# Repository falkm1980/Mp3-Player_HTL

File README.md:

# Mp3-Player_HTL
MP3 Player, HTL Saalfelden

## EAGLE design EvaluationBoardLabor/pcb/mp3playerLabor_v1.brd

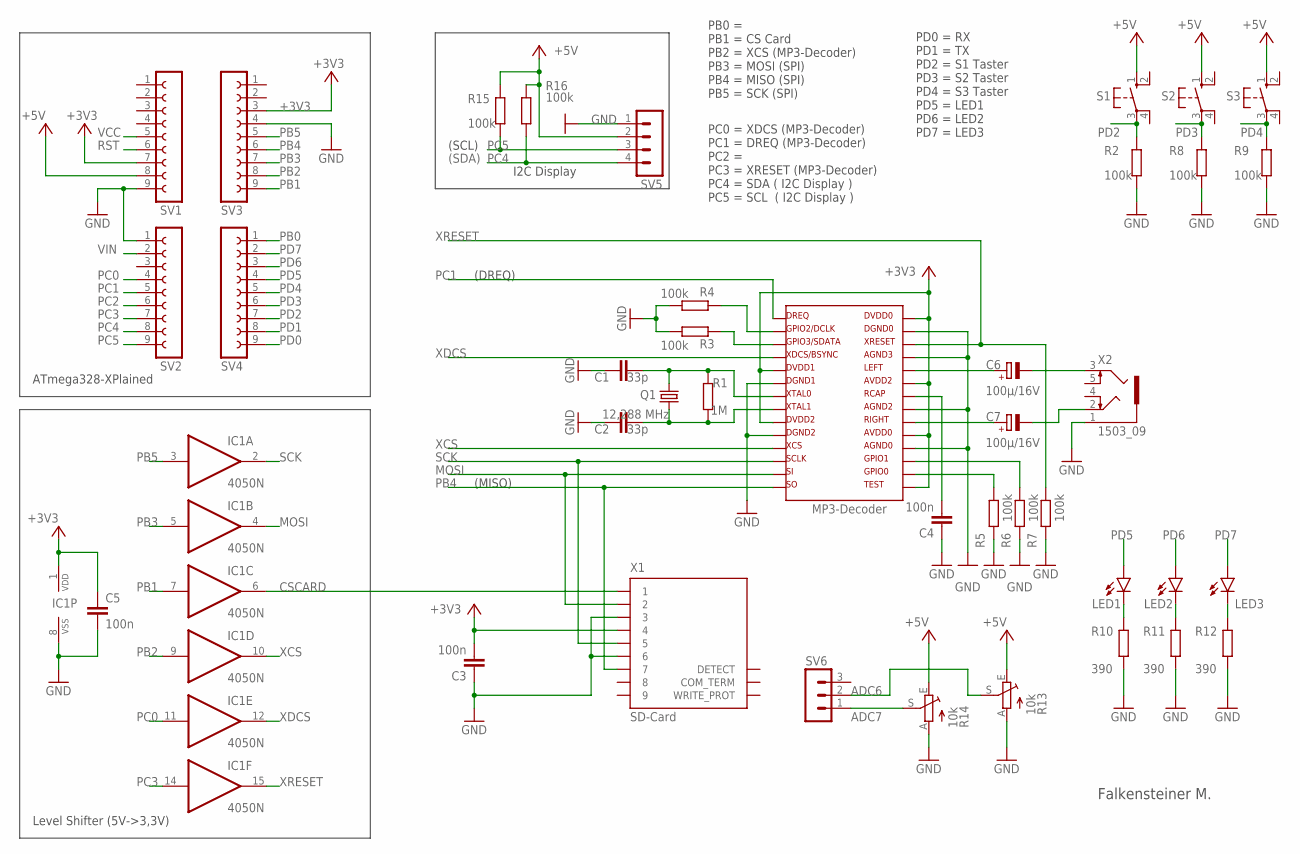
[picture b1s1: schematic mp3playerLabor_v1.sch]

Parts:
C1, C2: 33p; C1206K
C3, C4, C5: 100n; C1206K
C6, C7: 100µ/16V; UD-6,3X7,7_NICHICON
IC1: 4050N; DIL16
LED1, LED2, LED3: LEDSML1206; SML1206
Q1: 12,288 MHz; HC49UP
R1: 1M; R1206
R2, R3, R4, R5, R6, R7, R8, R9, R15, R16: 100k; R1206
R10, R11, R12: 390; R1206
R13, R14: 10k; CA6V
S1, S2, S3: 10-XX; B3F-10XX
SV1, SV2, SV3, SV4: FE09-1; FE09
SV5: MA04-1
SV6: MA03-1
U$1: VS1011; SOIC-28
X1: SD-Card; FPS009-3000
X2: 1503_09

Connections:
+3V3: C3.2, C5.1, IC1.1 (VDD), SV1.7, SV3.3, U$1.5, U$1.9, U$1.15, U$1.19, U$1.23, U$1.28, X1.4
+5V: R13.E, R14.E, R15.1, R16.1, S1.1 (S), S2.1 (S), S3.1 (S), SV1.8, SV5.2
ADC6: R13.S, SV6.2
ADC7: R14.S, SV6.1
CSCARD: IC1.6 (O), X1.1
GND: C1.1, C2.1, C3.1, C4.1, C5.2, IC1.8 (VSS), R2.2, R3.2, R4.2, R5.2, R6.2, R7.2, R8.2, R9.2, R10.2, R11.2, R12.2, R13.A, R14.A, SV1.9, SV2.1, SV3.4, SV5.1, U$1.6, U$1.10, U$1.18, U$1.21, U$1.25, U$1.27, X1.3, X1.6, X2.1
MOSI: IC1.4 (O), U$1.13, X1.2
unnamed: LED1.C, R10.1
unnamed: LED2.C, R11.1
unnamed: C2.2, Q1.1, R1.1, U$1.8
unnamed: LED3.C, R12.1
unnamed: C4.2, U$1.22
unnamed: R3.1, U$1.3
unnamed: C1.2, Q1.2, R1.2, U$1.7
unnamed: R4.1, U$1.2
unnamed: R6.1, U$1.17
unnamed: R5.1, U$1.16
unnamed: C7.+, U$1.20
unnamed: C6.+, U$1.24
unnamed: C6.-, X2.3
unnamed: C7.-, X2.2
PB0: SV4.1
PB1: IC1.7 (I), SV3.9
PB2: IC1.9 (I), SV3.8
PB3: IC1.5 (I), SV3.7
PB4: SV3.6, U$1.14, X1.7
PB5: IC1.3 (I), SV3.5
PC0: IC1.11 (I), SV2.4
PC1: SV2.5, U$1.1
PC2: SV2.6
PC3: IC1.14 (I), SV2.7
PC4: R16.2, SV2.8, SV5.4
PC5: R15.2, SV2.9, SV5.3
PD0: SV4.9
PD1: SV4.8
PD2: R2.1, S1.3, SV4.7
PD3: R8.1, S2.3, SV4.6
PD4: R9.1, S3.3, SV4.5
PD5: LED1.A, SV4.4
PD6: LED2.A, SV4.3
PD7: LED3.A, SV4.2
RST: SV1.6
SCK: IC1.2 (O), U$1.12, X1.5
VCC: SV1.5
VIN: SV2.2
XCS: IC1.10 (O), U$1.11
XDCS: IC1.12 (O), U$1.4
XRESET: IC1.15 (O), R7.1, U$1.26

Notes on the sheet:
Falkensteiner M.
PB0 = PB1 = CS Card PB2 = XCS (MP3-Decoder) PB3 = MOSI (SPI) PB4 = MISO (SPI) PB5 = SCK (SPI)
(MISO)
ATmega328-XPlained
PC0 = XDCS (MP3-Decoder) PC1 = DREQ (MP3-Decoder) PC2 = PC3 = XRESET (MP3-Decoder) PC4 = SDA ( I2C Display ) PC5 = SCL ( I2C Display )
Level Shifter (5V->3,3V)
PD0 = RX PD1 = TX PD2 = S1 Taster PD3 = S2 Taster PD4 = S3 Taster PD5 = LED1 PD6 = LED2 PD7 = LED3
MP3-Decoder
(DREQ)
(SCL)
(SDA)
I2C Display

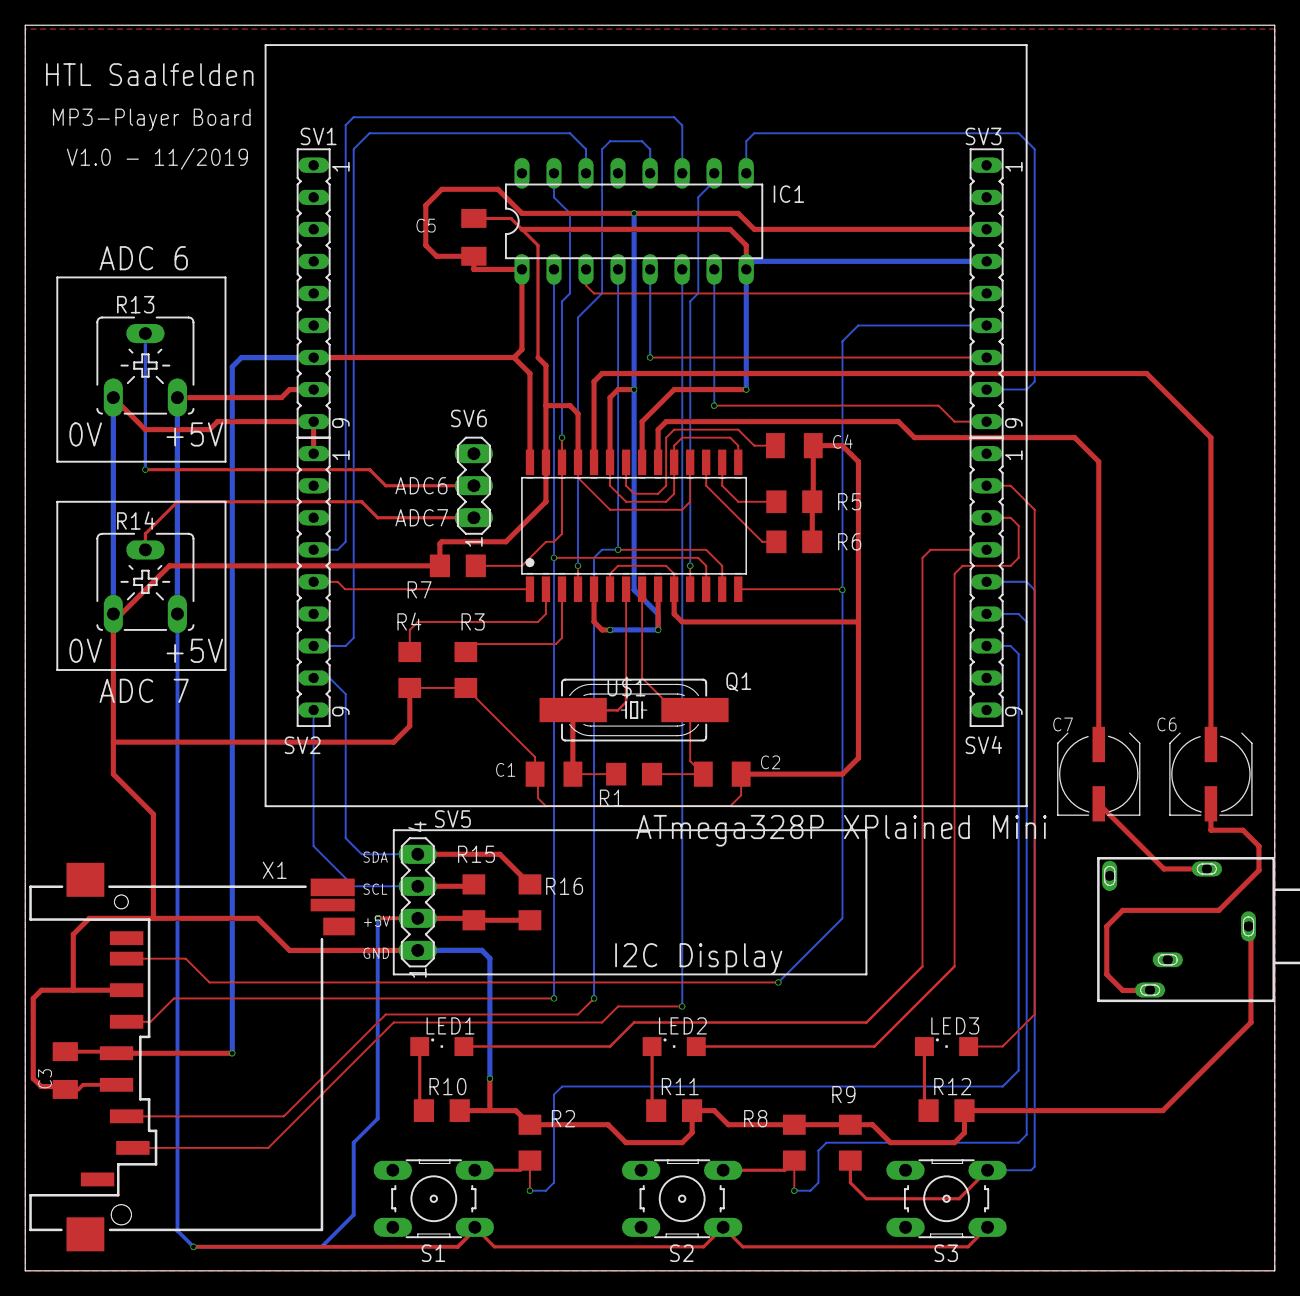
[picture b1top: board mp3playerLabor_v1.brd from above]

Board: 2 copper layers, 99.0 x 98.7 mm, 40 parts (0 on the bottom side), 41 nets.

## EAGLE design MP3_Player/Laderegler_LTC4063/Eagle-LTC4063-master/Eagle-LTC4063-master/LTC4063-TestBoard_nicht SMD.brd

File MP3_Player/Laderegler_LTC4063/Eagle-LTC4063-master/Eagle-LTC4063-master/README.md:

Eagle library for LTC4063
=========================

> Standalone Linear Li-Ion Charger with Micropower Low Dropout Linear Regulator

Eagle (v6.3) library for the LTC4063 Li-Ion Charger by Linear Technology. 

- Datasheet: http://cds.linear.com/docs/en/datasheet/4063fc.pdf
- Product Page: http://www.linear.com/product/LTC4063

License
-------

You are allowed to use the library for everything you want (including the distribution of this files) as long as you keep the Copyright notice in the library.

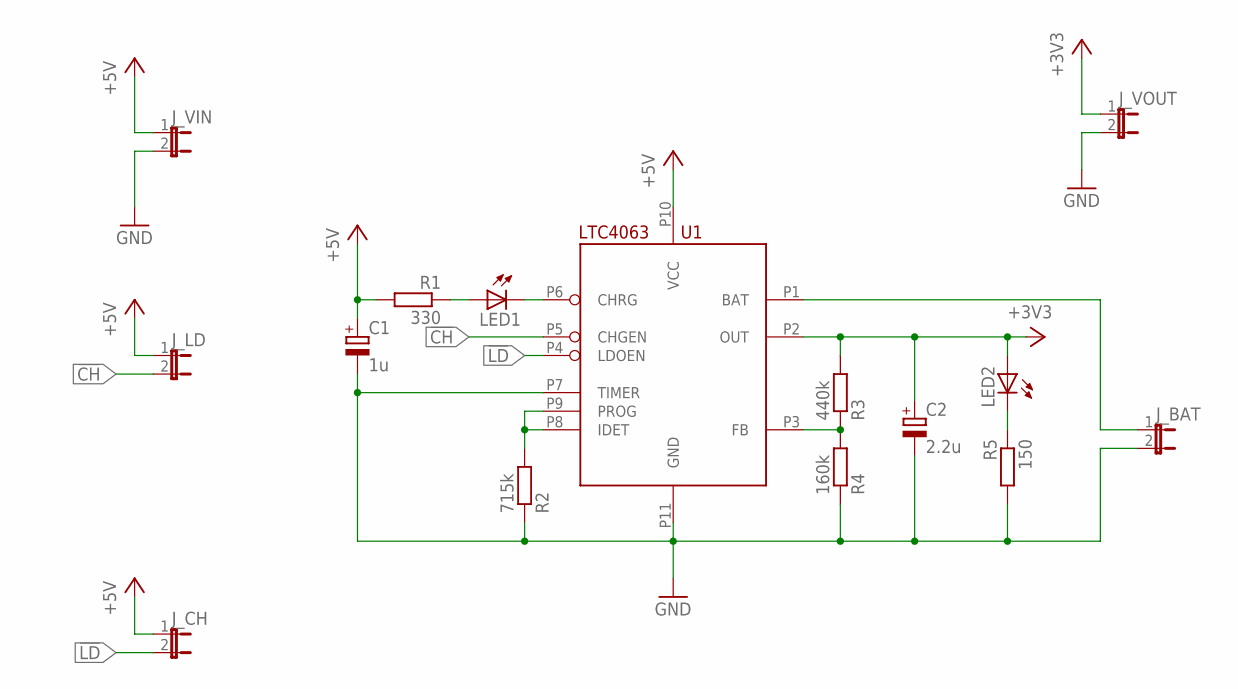
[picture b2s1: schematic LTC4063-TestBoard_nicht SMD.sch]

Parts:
C1: 1u; E2,5-6
C2: 2.2u; E2,5-6
J_BAT: JP1E; JP1
J_CH: JP1E; JP1
J_LD: JP1E; JP1
J_VIN: JP1E; JP1
J_VOUT: JP1E; JP1
LED1, LED2: LED3MM
R1: 330; 0207/7
R2: 715k; 0207/7
R3: 440k; 0207/7
R4: 160k; 0207/7
R5: 150; 0207/7
U1: LTC4063

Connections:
!CH: J_LD.2, U1.P5 (CHGEN)
!LD: J_CH.2, U1.P4 (LDOEN)
+3V3: C2.+, J_VOUT.1, LED2.A, R3.2, U1.P2 (OUT)
+5V: C1.+, J_CH.1, J_LD.1, J_VIN.1, R1.2, U1.P10 (VCC)
GND: C1.-, C2.-, J_BAT.2, J_VIN.2, J_VOUT.2, R2.1, R4.1, R5.2, U1.P7 (TIMER), U1.P11 (GND)
unnamed: R3.1, R4.2, U1.P3 (FB)
unnamed: J_BAT.1, U1.P1 (BAT)
unnamed: LED1.K (C), U1.P6 (CHRG)
unnamed: LED1.A, R1.1
unnamed: R2.2, U1.P8 (IDET), U1.P9 (PROG)
unnamed: LED2.K (C), R5.1

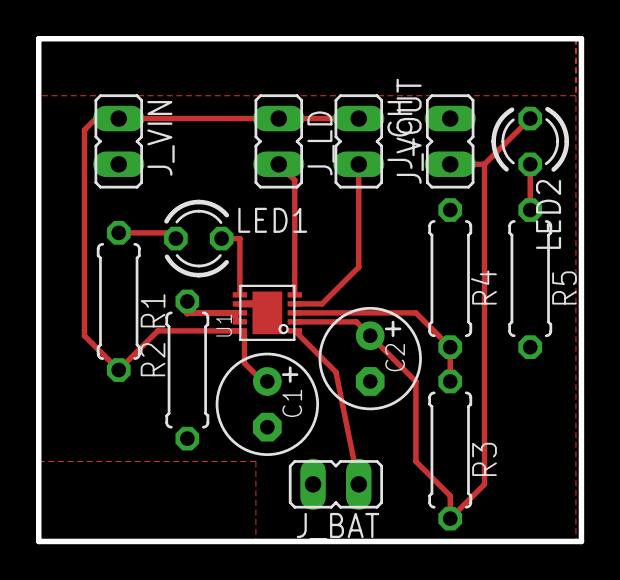
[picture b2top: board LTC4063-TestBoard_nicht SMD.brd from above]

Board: 2 copper layers, 30.1 x 27.9 mm, 15 parts (0 on the bottom side), 11 nets.

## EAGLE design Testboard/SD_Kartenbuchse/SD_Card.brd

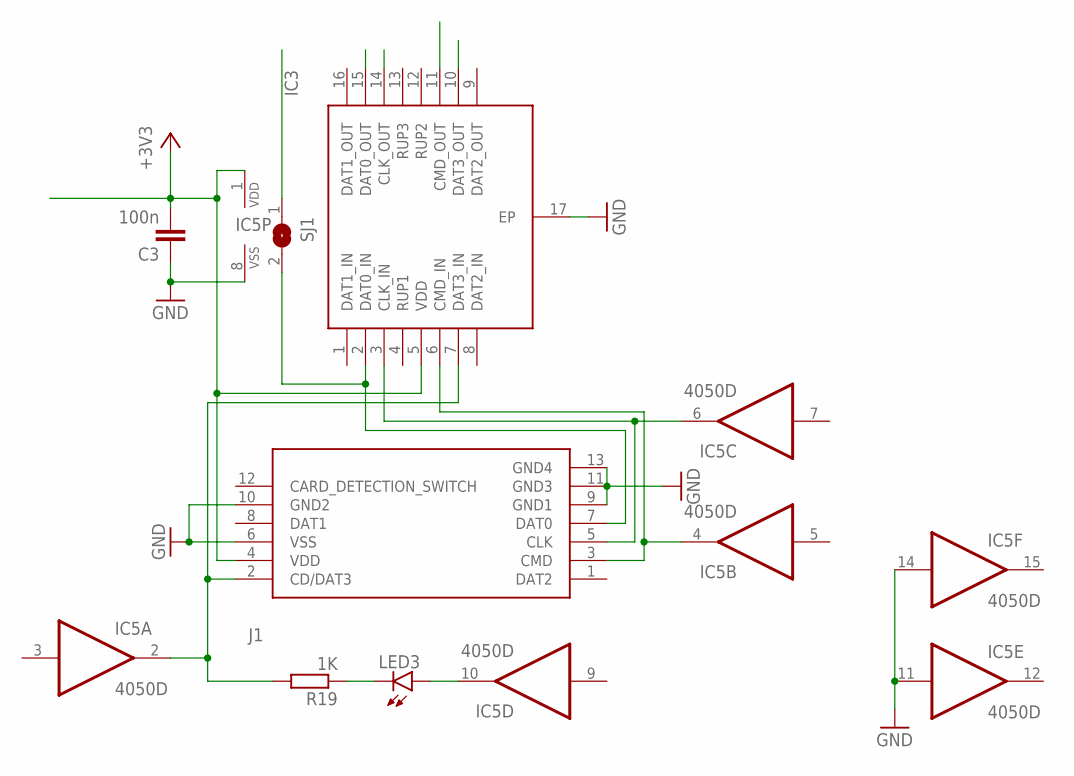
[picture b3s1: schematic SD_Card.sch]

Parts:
C3: 100n; C1206K
IC3: ECLAMP2410P.TCT; SON50P160X400X65-17N
IC5: 4050D; SO16
J1: DM3CS-SF
LED3: LG_T679-E1F1-1; PLCC2
R19: 1K; R1206
SJ1: SJ

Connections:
+3V3: C3.2, IC3.5 (VDD), IC5.1 (VDD), J1.4 (VDD)
GND: C3.1, IC3.17 (EP), IC5.8 (VSS), IC5.11 (I), IC5.14 (I), J1.6 (VSS), J1.9 (GND1), J1.10 (GND2), J1.11 (GND3), J1.13 (GND4)
unnamed: IC3.15 (DAT0_OUT), SJ1.1
unnamed: IC5.10 (O), LED3.A
unnamed: LED3.C, R19.1
unnamed: IC3.7 (DAT3_IN), IC5.2 (O), J1.2 (CD/DAT3), R19.2
unnamed: IC3.2 (DAT0_IN), J1.7 (DAT0), SJ1.2
unnamed: IC3.3 (CLK_IN), IC5.6 (O), J1.5 (CLK)
unnamed: IC3.6 (CMD_IN), IC5.4 (O), J1.3 (CMD)

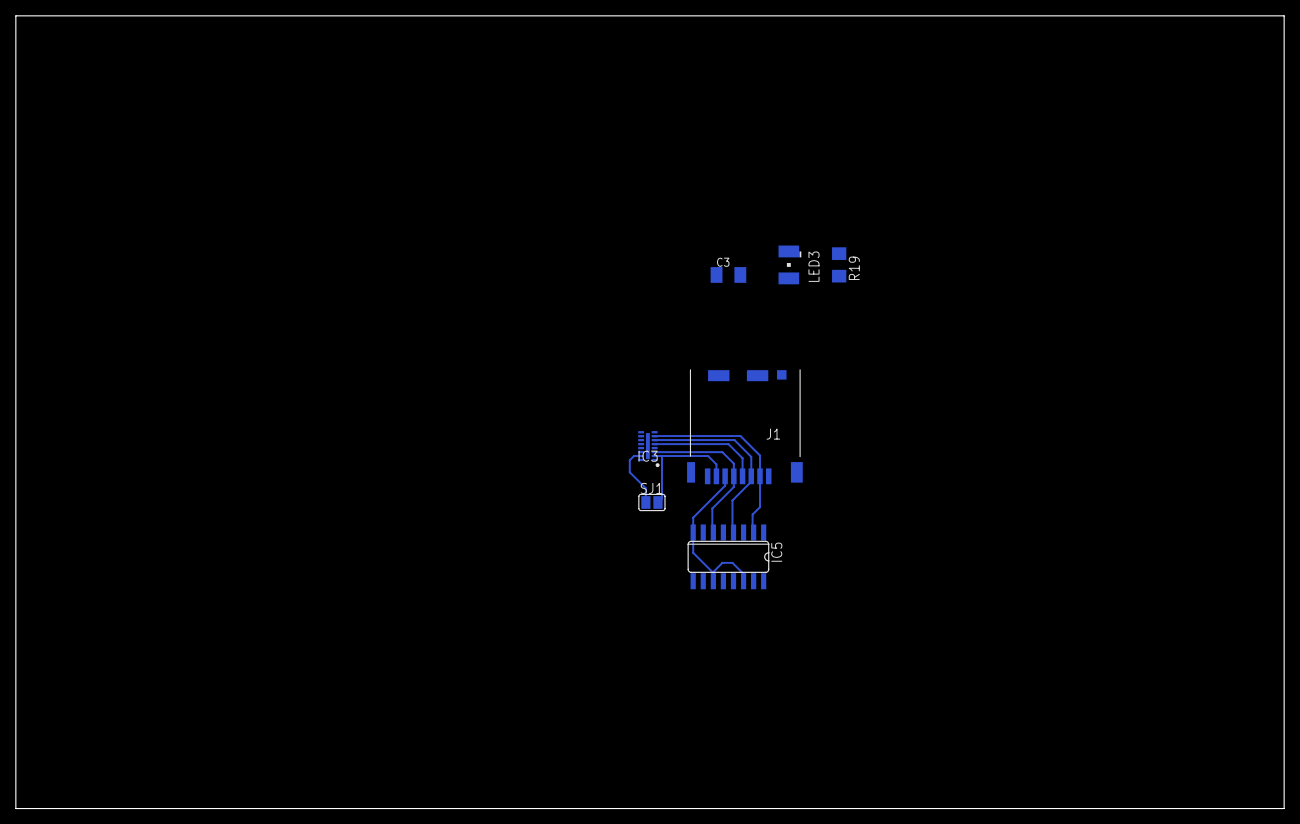
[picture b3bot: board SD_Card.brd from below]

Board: 2 copper layers, 160.0 x 100.0 mm, 7 parts (7 on the bottom side), 9 nets.

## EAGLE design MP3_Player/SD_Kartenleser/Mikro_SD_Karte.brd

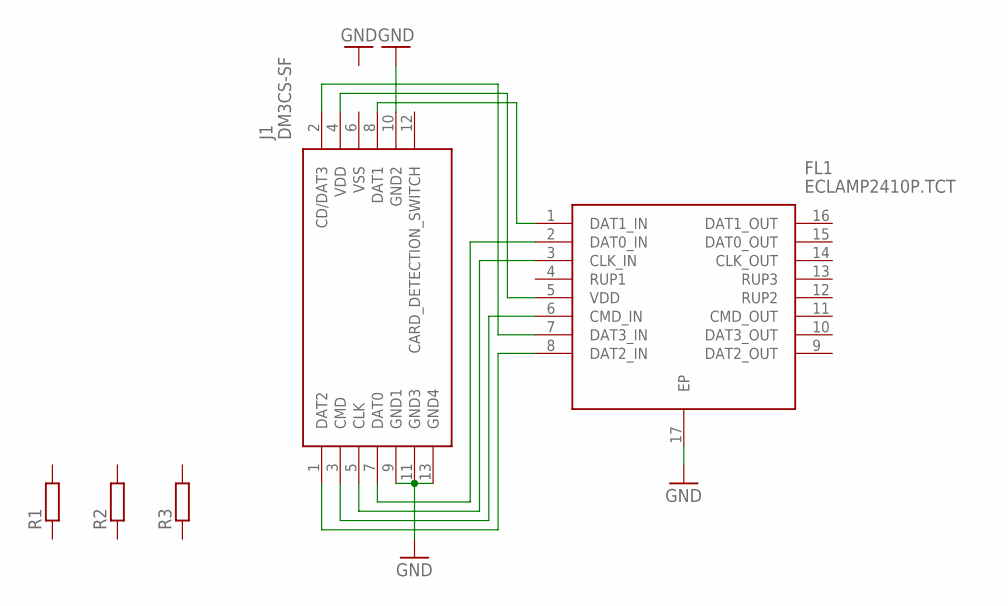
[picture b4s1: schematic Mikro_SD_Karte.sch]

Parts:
FL1: ECLAMP2410P.TCT; SON50P160X400X65-17N
J1: DM3CS-SF
R1, R2, R3: R-EU_R0603; R0603

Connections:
GND: FL1.17 (EP), J1.9 (GND1), J1.10 (GND2), J1.11 (GND3), J1.13 (GND4)
unnamed: FL1.1 (DAT1_IN), J1.8 (DAT1)
unnamed: FL1.8 (DAT2_IN), J1.1 (DAT2)
unnamed: FL1.5 (VDD), J1.4 (VDD)
unnamed: FL1.7 (DAT3_IN), J1.2 (CD/DAT3)
unnamed: FL1.2 (DAT0_IN), J1.7 (DAT0)
unnamed: FL1.3 (CLK_IN), J1.5 (CLK)
unnamed: FL1.6 (CMD_IN), J1.3 (CMD)

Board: 2 copper layers, 5 parts (0 on the bottom side), 8 nets, no tracks yet.

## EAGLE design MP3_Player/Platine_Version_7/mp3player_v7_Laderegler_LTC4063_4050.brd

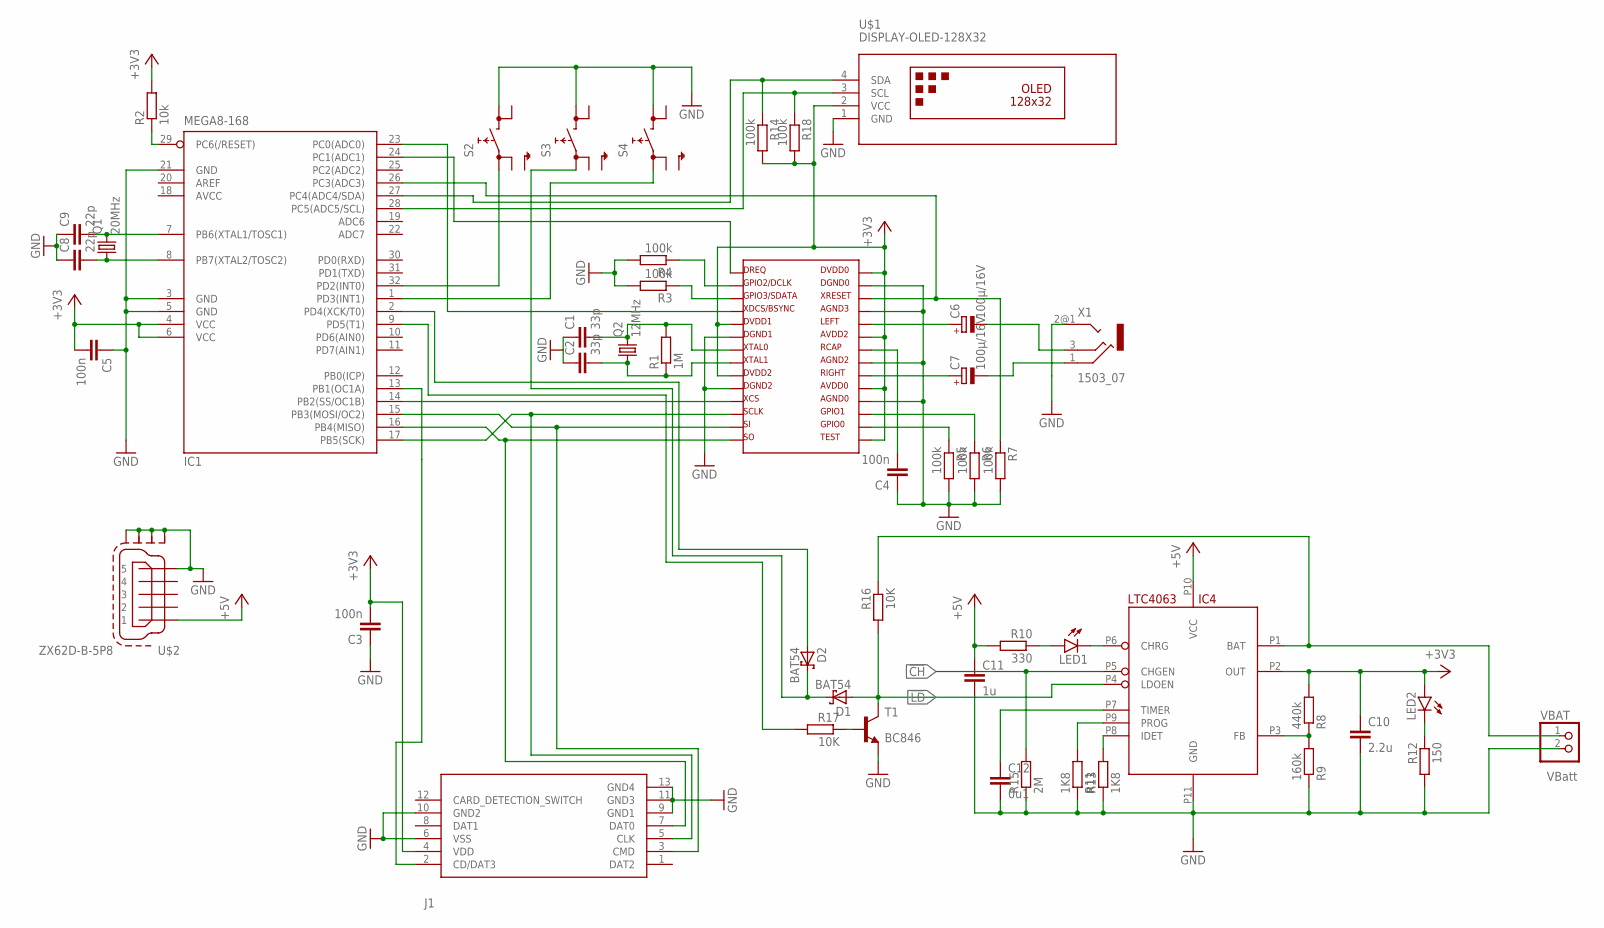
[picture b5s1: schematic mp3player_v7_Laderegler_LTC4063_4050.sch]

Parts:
C1, C2: 33p; C1206K
C3, C4, C5: 100n; C1206K
C6, C7: 100µ/16V; UD-6,3X7,7_NICHICON
C8, C9: 22p; C1206K
C10: 2.2u; C0805K
C11: 1u; C0805K
C12: 0u1; C0805K
D1, D2: BAT54; SOT23
IC1: MEGA8-168; TQFP32-08
IC2: VS1011; SOIC-28
IC4: LTC4063
J1: DM3CS-SF
LED1, LED2: LG_T679-E1F1-1; PLCC2
Q1: 20MHz; HC49UP
Q2: 12MHz; HC49UP
R1: 1M; R0805
R2: 10k; 0207/7
R3, R4, R5, R6, R14, R18: 100k; R0805
R7: 100k; 0207/15
R8: 440k; R0805
R9: 160k; R0805
R10: 330; R0805
R11, R13: 1K8; R0805
R12: 150; R0805
R15: 2M; R0805
R16: 10K; 0207/7
R17: 10K; R0805
S2, S3, S4: SKHMPSE010; SKHMPXE010
T1: BC846; SOT23
U$1: DISPLAY-OLED-128X32
U$2: ZX62D-B-5P8
VBAT: PINHD-1X2; 1X02
X1: 1503_07

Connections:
!CH: IC4.P5 (CHGEN), R15.2
!LD: D1.1 (A), IC4.P4 (LDOEN), R16.2, T1.3 (C)
+3V3: C3.2, C5.2, C10.1, IC1.4 (VCC), IC1.6 (VCC), IC2.5, IC2.9, IC2.15, IC2.19, IC2.23, IC2.28, IC4.P2 (OUT), J1.4 (VDD), LED2.A, R2.2, R8.2, R14.2, R18.2, U$1.2 (VCC)
+5V: C11.1, IC4.P10 (VCC), R10.2, U$2.P$1 (1)
AVCC: IC1.18 (AVCC)
GND: C1.1, C2.1, C3.1, C4.1, C5.1, C8.1, C9.1, C10.2, C11.2, C12.2, IC1.3 (GND), IC1.5 (GND), IC1.21 (GND), IC2.6, IC2.10, IC2.18, IC2.21, IC2.25, IC2.27, IC4.P11 (GND), J1.6 (VSS), J1.9 (GND1), J1.10 (GND2), J1.11 (GND3), J1.13 (GND4), R3.2, R4.2, R5.2, R6.2, R7.2, R9.1, R11.1, R12.2, R13.1, R15.1, S2.3 (2.1), S3.3 (2.1), S4.3 (2.1), T1.2 (E), U$1.1 (GND), U$2.P$5 (5), U$2.SH1, U$2.SH2, U$2.SH3, U$2.SH4, VBAT.2, X1.2@1 (2)
unnamed: IC1.17 (PB5(SCK)), IC2.12, J1.5 (CLK)
unnamed: IC1.16 (PB4(MISO)), IC2.14, J1.7 (DAT0)
unnamed: IC1.15 (PB3(MOSI/OC2)), IC2.13, J1.3 (CMD)
unnamed: IC1.14 (PB2(SS/OC1B)), IC2.11
unnamed: C2.2, IC2.8, Q2.1, R1.1
unnamed: IC1.23 (PC0(ADC0)), IC2.4
unnamed: C4.2, IC2.22
unnamed: IC2.3, R3.1
unnamed: C1.2, IC2.7, Q2.2, R1.2
unnamed: IC2.2, R4.1
unnamed: IC1.32 (PD2(INT0)), S2.1 (1.1)
unnamed: IC2.17, R6.1
unnamed: IC2.16, R5.1
unnamed: IC1.24 (PC1(ADC1)), IC2.1
unnamed: D2.1 (A), IC1.2 (PD4(XCK/T0))
unnamed: IC1.26 (PC3(ADC3)), IC2.26, R7.1
unnamed: IC1.29 (PC6(/RESET)), R2.1
unnamed: C7.+, IC2.20
unnamed: C6.+, IC2.24
unnamed: IC1.1 (PD3(INT1)), S4.1 (1.1)
unnamed: C6.-, X1.3
unnamed: C7.-, X1.1
unnamed: C8.2, IC1.8 (PB7(XTAL2/TOSC2)), Q1.1
unnamed: C9.2, IC1.7 (PB6(XTAL1/TOSC1)), Q1.2
unnamed: IC4.P3 (FB), R8.1, R9.2
unnamed: IC4.P1 (BAT), R16.1, VBAT.1
unnamed: LED1.A, R10.1
unnamed: IC4.P9 (PROG), R11.2
unnamed: IC4.P6 (CHRG), LED1.C
unnamed: LED2.C, R12.1
unnamed: IC4.P8 (IDET), R13.2
unnamed: C12.1, IC4.P7 (TIMER)
unnamed: IC1.27 (PC4(ADC4/SDA)), R14.1, U$1.4 (SDA)
unnamed: IC1.28 (PC5(ADC5/SCL)), R18.1, U$1.3 (SCL)
unnamed: IC1.13 (PB1(OC1A)), J1.2 (CD/DAT3)
unnamed: R17.1, T1.1 (B)
unnamed: IC1.9 (PD5(T1)), R17.2
unnamed: D1.3 (C), D2.3 (C), S3.1 (1.1)

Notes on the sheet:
VBatt

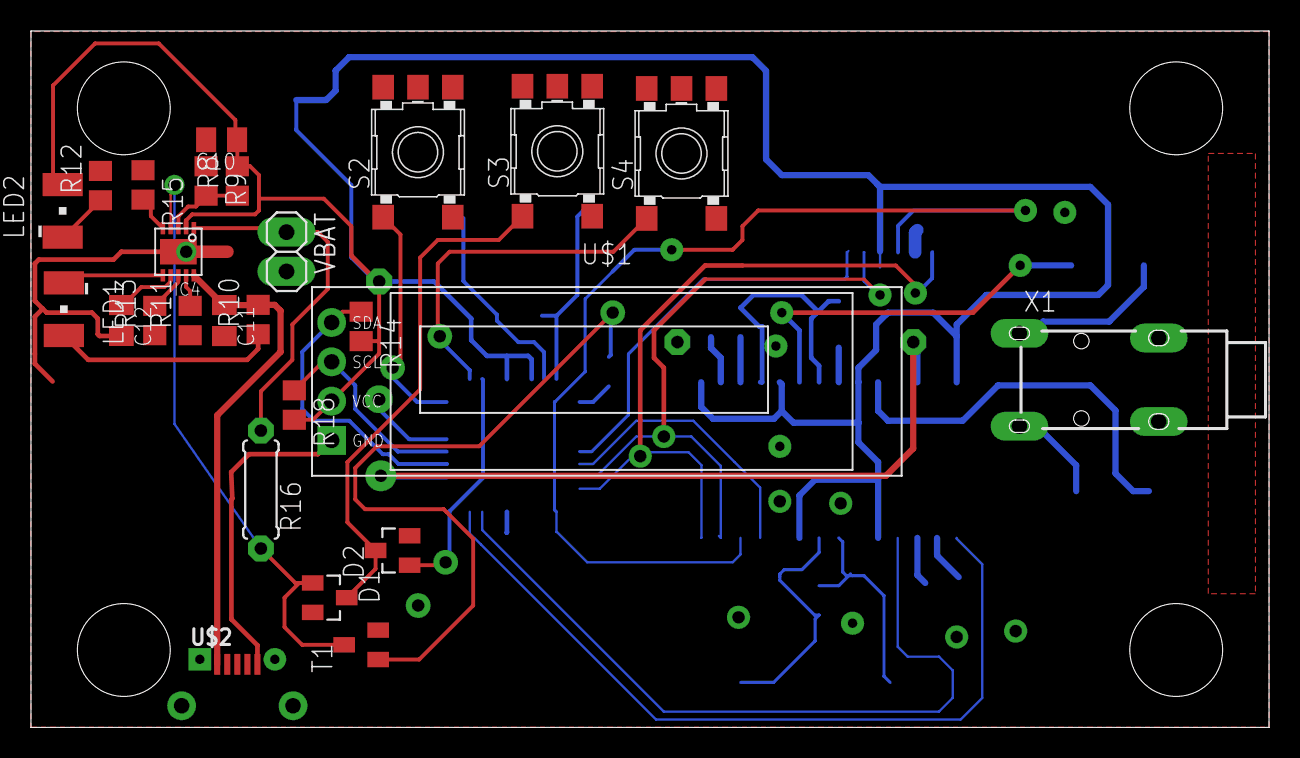
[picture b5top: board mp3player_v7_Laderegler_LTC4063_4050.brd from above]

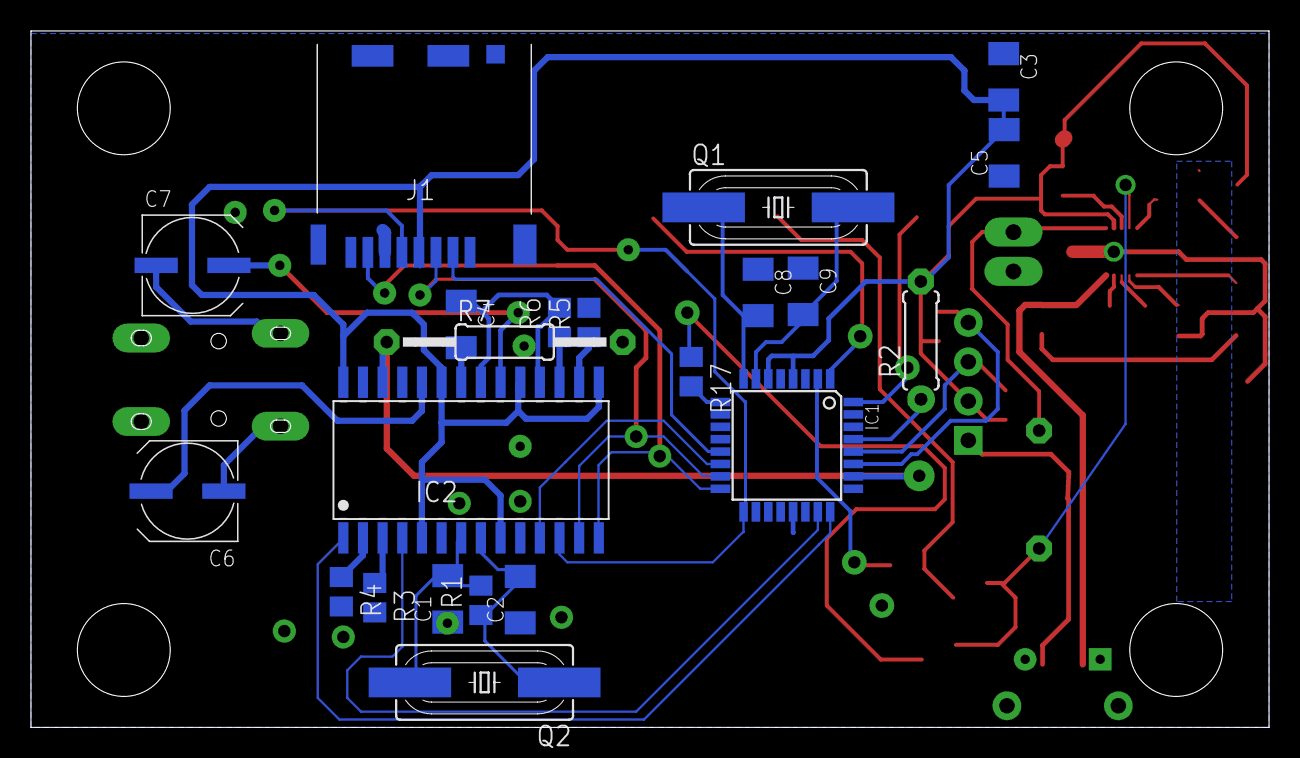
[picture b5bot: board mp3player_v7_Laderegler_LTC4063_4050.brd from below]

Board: 2 copper layers, 80.0 x 45.0 mm, 48 parts (22 on the bottom side), 43 nets.

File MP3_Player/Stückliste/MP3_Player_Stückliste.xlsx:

|  | Stückliste MP3 Player |  | RS |  |  |  | Bibliothek
Pos | Stück | Bezeichnung | Beschreibung | Bestellnummer | Gehäuse | Lieferant | Preis
 |  | ATMEGA 168 | Prozessor | 922-0749
 |  | VS1011E | Audio IC
 |  | BTM-222_Serial | Bluetooth
 |  | Quarz | 20MHz | 148-5634
 |  | Quarz | 12MHz | 148-5359
 |  | Klinkenbuchse |  | 909-2238 | Testboard | RS | 1.3859999999999999
 |  | Klinkenbuchse | RS | 513-0421 | Testboard | RS | 1.42 | con_Hirschmann
 |  | Klinkenbuchse | Reichelt | LUM1503-02 | SMD | Reichelt
 |  | Klinkenbuchse | Reichelt | LUM1503-07 | Draht | Reichelt
 |  | LTC3455 |  | 153-3383
 |  | Elko | 10µ | 136-2654 | 1206 |  | 0.158
 |  | Elko | 47µ | 136-2598 | 1206
 |  | Kondensator | 27pF | 169-9964
 |  | LED Rot |  | 862-4695 |  |  | 9.7000000000000003E-2
 |  | LED Grün |  | 862-4691 |  |  | 0.1
 |  | LTC4063 | Mouser
 |  | Accu | Conrad | 252031-62
 |  | Accu | Mouser | 406-ASR00035
 |  | Gehäuse | Nedis | BOX G404
 |  | Akku | Reichelt | Akku 30083
 |  | Akku | Reichelt | AKKU CP 38 | 500mA
 |  | USB | RS | 136-2263
 |  | C1 | 33p | Bestellnummer | R1206
 |  | C2 | 33p |  | R1206
 |  | C3 | 100n |  | R1206
 |  | C4 | 100n |  | R1206
 |  | C5 | 100n |  | R1206
 |  | C6 | 100µ/16V |  | DU-6,3x7,7
 |  | C7 | 100µ/16V |  | DU-6,3x7,8
 |  | C8 | 22p |  | R1206
 |  | C9 | 22p |  | R1206
 |  | C10 | 2,2µ |  | R0805
 |  | C11 | 1µ |  | R0805
 |  | C12 | 0,1µ |  | R0805
 |  | R1 | 1M |  | R0805
 |  | R2 | 10K |  | 0207/10
 |  | R3 | 100K |  | R1206
 |  | R4 | 100K |  | R1206
 |  | R5 | 100K |  | R0805
 |  | R6 | 100K |  | R0806
 |  | R7 | 100K |  | R1206
 |  | R8 | 440K |  | R0806
 |  | R9 | 160K |  | R0806
 |  | R10 | 330R |  | R0806
 |  | R11 | 1k8 |  | R0806
 |  | R12 | 150R |  | R0806
 |  | R13 | 1K8 |  | R1206
 |  | R14 | 100K |  | R0806
 |  | R15 | 2M |  | R0806
 |  | R16 | 10K |  | 0207/10
 |  | R17 | 10K |  | 0207/10
 |  | R18 | 100K |  | 0207/10
 |  | R19 | 1K |  | 0207/10

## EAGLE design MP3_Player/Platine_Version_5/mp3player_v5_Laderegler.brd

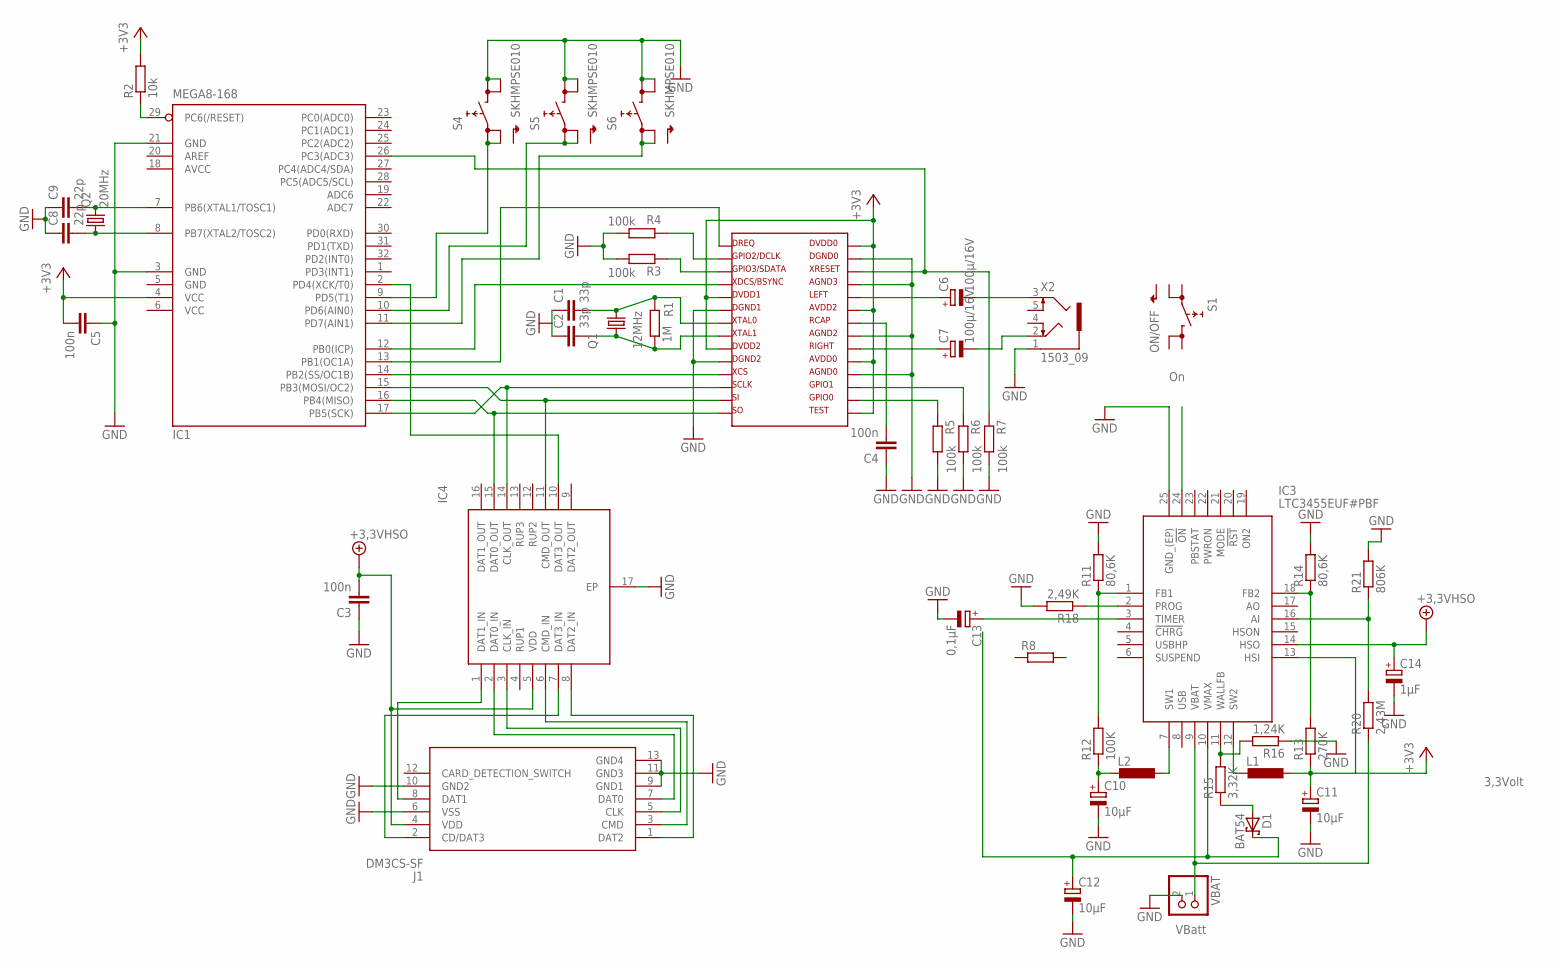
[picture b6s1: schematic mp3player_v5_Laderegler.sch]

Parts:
C1, C2: 33p; C1206K
C3, C4, C5: 100n; C1206K
C6, C7: 100µ/16V; UD-6,3X7,7_NICHICON
C8, C9: 22p; C1206K
C10, C11, C12: 10µF; 153CLV-0505
C13: 0,1µF; B/3528-21W
C14: 1µF; B/3528-21W
D1: BAT54; SOT23
IC1: MEGA8-168; TQFP32-08
IC2: VS1011; SOIC-28
IC3: LTC3455EUF#PBF; QFN50P400X400X80-25N
IC4: ECLAMP2410P.TCT; SON50P160X400X65-17N
J1: DM3CS-SF
L1, L2: L-EUL2825P; L2825P
Q1: 12MHz; HC49UP
Q2: 20MHz; HC49UP
R1: 1M; R0805
R2: 10k; R0805
R3, R4, R5, R6, R7: 100k; R0805
R8: R-EU_R0805; R0805
R11, R14: 80,6K; R0805
R12: 100K; M1206
R13: 270K; M1206
R15: 3,32K; M1206
R16: 1,24K; M1206
R18: 2,49K; R0805
R20: 2,43M; M1206
R21: 806K; R0805
S1: ON/OFF; SKHMPXE010
S4, S5, S6: SKHMPSE010; SKHMPXE010
VBAT: PINHD-1X2; 1X02
X2: 1503_09

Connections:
+3,3VHSO: C3.2, C14.+, IC3.14 (HSO), IC4.5 (VDD), J1.4 (VDD)
+3V3: C5.2, C11.+, IC1.4 (VCC), IC2.5, IC2.9, IC2.15, IC2.19, IC2.23, IC2.28, IC3.13 (HSI), L1.1, R2.2, R13.1
AVCC: IC1.18 (AVCC)
GND: C1.1, C2.1, C3.1, C4.1, C5.1, C8.1, C9.1, C10.-, C11.-, C12.-, C13.-, C14.-, IC1.3 (GND), IC1.5 (GND), IC1.21 (GND), IC2.6, IC2.10, IC2.18, IC2.21, IC2.25, IC2.27, IC3.25 (GND_(EP)), IC4.17 (EP), J1.6 (VSS), J1.9 (GND1), J1.10 (GND2), J1.11 (GND3), J1.13 (GND4), R3.2, R4.2, R5.2, R6.2, R7.2, R11.2, R14.2, R16.1, R18.2, R21.2, S4.3 (2.1), S4.4 (2.2), S5.3 (2.1), S5.4 (2.2), S6.3 (2.1), S6.4 (2.2), VBAT.2, X2.1
unnamed: IC1.17 (PB5(SCK)), IC2.12, IC4.14 (CLK_OUT)
unnamed: IC1.16 (PB4(MISO)), IC2.14, IC4.15 (DAT0_OUT)
unnamed: IC1.15 (PB3(MOSI/OC2)), IC2.13, IC4.11 (CMD_OUT)
unnamed: IC1.14 (PB2(SS/OC1B)), IC2.11
unnamed: IC1.2 (PD4(XCK/T0)), IC4.10 (DAT3_OUT)
unnamed: C2.2, IC2.8, Q1.1, R1.1
unnamed: IC1.12 (PB0(ICP)), IC2.4
unnamed: C4.2, IC2.22
unnamed: IC2.3, R3.1
unnamed: C1.2, IC2.7, Q1.2, R1.2
unnamed: IC2.2, R4.1
unnamed: IC1.9 (PD5(T1)), S4.1 (1.1), S4.2 (1.2)
unnamed: IC2.17, R6.1
unnamed: IC2.16, R5.1
unnamed: IC1.13 (PB1(OC1A)), IC2.1
unnamed: IC1.10 (PD6(AIN0)), S5.1 (1.1), S5.2 (1.2)
unnamed: IC1.26 (PC3(ADC3)), IC2.26, R7.1
unnamed: IC1.29 (PC6(/RESET)), R2.1
unnamed: C7.+, IC2.20
unnamed: C6.+, IC2.24
unnamed: IC1.11 (PD7(AIN1)), S6.1 (1.1), S6.2 (1.2)
unnamed: C6.-, X2.3
unnamed: C7.-, X2.2
unnamed: C8.2, IC1.8 (PB7(XTAL2/TOSC2)), Q2.1
unnamed: C9.2, IC1.7 (PB6(XTAL1/TOSC1)), Q2.2
unnamed: IC4.1 (DAT1_IN), J1.8 (DAT1)
unnamed: IC4.8 (DAT2_IN), J1.1 (DAT2)
unnamed: IC3.12 (SW2), L1.2
unnamed: IC4.7 (DAT3_IN), J1.2 (CD/DAT3)
unnamed: IC4.2 (DAT0_IN), J1.7 (DAT0)
unnamed: IC4.3 (CLK_IN), J1.5 (CLK)
unnamed: IC4.6 (CMD_IN), J1.3 (CMD)
unnamed: IC3.7 (SW1), L2.1
unnamed: IC3.1 (FB1), R11.1, R12.2
unnamed: C10.+, L2.2, R12.1
unnamed: IC3.18 (FB2), R13.2, R14.1
unnamed: IC3.9 (VBAT), R20.1, VBAT.1
unnamed: C12.+, D1.3 (C), IC3.10 (VMAX)
unnamed: IC3.11 (WALLFB), R15.2, R16.2
unnamed: D1.1 (A), R15.1
unnamed: IC3.2 (PROG), R18.1
unnamed: C13.+, IC3.3 (TIMER)
unnamed: IC3.16 (AI), R20.2, R21.1
VCC: IC1.6 (VCC)

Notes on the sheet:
3,3Volt
VBatt

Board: 2 copper layers, 47 parts (45 on the bottom side), 46 nets, no tracks yet.

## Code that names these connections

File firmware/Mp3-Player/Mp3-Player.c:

/*
* Mp3_Player.c
*
* Created: 11.12.2011 21:18:14
*  Author: Markus
*/
#define F_CPU 16000000UL
#include <avr/io.h>
#include "lcd.h"
#include <util/delay.h>
#include "MMC/pff.h"
#include "MP3Decoder/vs1011.h"

//#define KEY_BACK	PD0
//#define KEY_PLAY	PD1
#define KEY_BACK	PD2
#define KEY_PLAY	PD4
#define KEY_FORWARD	PD3

#define BACK			1
#define PLAY			2
#define FORWARD			3
#define VOLUME_MINUS	4
#define VOLUME_PLUS		5

uint8_t iBackDown = 0;
uint8_t iPlayDown = 0;
uint8_t iForwardDown = 0;
uint8_t iLastValue = 0xFF;
uint8_t iVolumePressed = 0;

void InitKeyboard()
{
	DDRD = ~((1<<KEY_PLAY) | (1<<KEY_BACK) | (1<<KEY_FORWARD));
	// the CS for the card is also in PORTD but this PIN is initialized in spi.c->init_spi
	// therefore it is important that InitKeyboard is called before init_spi
}

//void InitUART()
//{
	//UCSR0B = (1 << TXEN0) | (1 << RXEN0);
	//UCSR0C = (1 << UCSZ00) | (1 << UCSZ01);
	//
	//UBRR0 = 25;
//}

void InitUART()
{
	UCSR0B = (1 << TXEN0) | (1 << RXEN0);// | (1 << RXCIE0);
	UCSR0C = (1 << UCSZ00) | (1 << UCSZ01);
	
	UBRR0 = 51;	// Bluetooth module has 19200 baud, 51 = value @16MHz clock for 19200
}

/*
* tries to read a byte from the serial port (bluetooth)
*/
//uint8_t ReadSerialByte()
//{
	//uint8_t rcv = 0x00;
	//
	//while((UCSR0A & (1 << RXC0)) == 0x00)
	//{
	//}
	//
	//rcv = UDR0;
	//return rcv;
//}

void USART_Transmit( unsigned char data )
{
	/* Wait for empty transmit buffer */
	while ( !( UCSR0A & (1<<UDRE0)) )
	;
	/* Put data into buffer, sends the data */
	UDR0 = data;
}

void SendString(uint8_t* pData)
{
	uint8_t len = strlen(pData);
	if (len < 1)
		return;
	
	char c = 0x00;
	
	while(c = *pData++)
		USART_Transmit(c);
	
	USART_Transmit('\r\n');
}

uint8_t ReadSerialByte()
{
	uint8_t rcv = 0x00;
	
	if ((UCSR0A & (1 << RXC0)) != 0x00)
	{
		rcv = UDR0;
		switch(rcv)
		{
			case 0x01:
			case 0x31:
				return 1;
			
			case 0x02:
			case 0x32:
				return 2;
				
			case 0x03:
			case 0x33:
				return 3;
				
			default:
				return rcv;
		}
	}
	else
		return 0x00;
}

uint8_t GetKey()
{
	//uint8_t serialData = 0x00;
	//serialData = ReadSerialByte();
	//if (serialData != 0x00)
		//return serialData;
	
	uint8_t portD = PIND;
	if (portD == iLastValue)
		return 0;
	
	iLastValue = portD;
	// PD3, S4
	if (iPlayDown && (portD & 0x10))
	{
		iPlayDown = 0;
		if (iVolumePressed != 0)
		{
			iVolumePressed = 0;
			return 0;
		}
		
		return 2;
	}

	// check Volume
	if (iPlayDown)
	{
		// PD2, S2
		if ((portD & 0x08) == 0x00)
		{
			iVolumePressed = 1;
			return 5;
		}
		// PD4, S3
		if ((portD & 0x04) == 0x00)
		{
			iVolumePressed = 1;
			return 4;
		}
	}

	// PD2, S2
	if (iBackDown && (portD & 0x04))
	{
		iBackDown = 0;
		return 1;
	}	

	// PD4, S3
	if (iForwardDown && (portD & 0x08))
	{
		iForwardDown = 0;
		return 3;
	}
	
	
	// PD2, S2
	if ((portD & 0x04) == 0x00)
	{
		if (!iBackDown)
		{
			iBackDown = 1;
			return 0;			
		}
	}
	// PD3, S4
	if ((portD & 0x10) == 0x00)
	{
		if (!iPlayDown)
		{
			iPlayDown = 1;
			return 0;
		}
	}
	//PD4, S3
	if ((portD & 0x08) == 0x00)
	{
		if (!iForwardDown)
		{
			iForwardDown = 1;
			return 0;
		}
	}
		
	return 0;
}


uint8_t GetNumberFiles()
{
	DIR dir;
	char* path = "";
	BYTE res = 0;
	res = pf_opendir(&dir, path);
	uint8_t numFiles = 0;
	
	if (res == FR_OK)
	{
		while (1)
		{
			FILINFO fno;
			res = pf_readdir(&dir, &fno);
			if (res != FR_OK || fno.fname[0] == 0)
			{
				break;
			}
			numFiles++;
		}
	}

	return numFiles;
}

uint8_t PlayFile(uint8_t numFile2Play)
{
	BYTE res = 0;

	DIR dir;
	char* path = "";
	res = pf_opendir(&dir, path);
	FILINFO fno;
	
	if (res == FR_OK)
	{
		uint8_t index = 0;
		do
		{
			res = pf_readdir(&dir, &fno);
			if (res != FR_OK || fno.fname[0] == 0)
			{
				break;
			}
			
			index++;
		} while(index < numFile2Play);
	}
	else
	{
		return 0;
	}
	
	SoftwareReset();	// resets the MP3-Chip
	
	SendString(fno.fname);

	res = pf_open(fno.fname);
	if (res)
	{
//		StartSineTest();
		_delay_ms(100);
		return 0;
	}

	const WORD sizeBlock = 512;
	BYTE buff[sizeBlock];
	WORD br=0;
	uint8_t serialData = 0x00;
	uint16_t powerOffRepeat = 0;
	
	while(1)
	{
		res = pf_read(buff, sizeBlock, &br);    // Read data to the buff[]
		if (res != 0)
		{
			break;
		}
		else
		{
			
			if (br == 0)
			{
				break;
			}
			
			uint16_t bytesWritten = 0;
			do
			{
				uint16_t bytes2Write = 0;
				if ((br - bytesWritten) > 32)
				bytes2Write = 32;
				else
				bytes2Write = br - bytesWritten;
				
				for(int i=0; i<32; i++)
				{
					WriteMP3DataByte(buff[bytesWritten+i]);
				}
				
				bytesWritten += bytes2Write;
				
				loop_until_bit_is_set(PINC, PC1);
				
				switch(GetKey())
				{
					case BACK:
						_delay_ms(100);
						return 1;
					case PLAY:
						_delay_ms(100);
						return 2;
					case FORWARD:
						_delay_ms(100);
						return 3;
					case VOLUME_MINUS:
						VolumeMinus();
						_delay_ms(50);
						break;
					case VOLUME_PLUS:
						VolumePlus();
						_delay_ms(50);
						break;
					default:
						if ((PIND & 0x04) == 0)
						{
							powerOffRepeat++;
							if (powerOffRepeat > 1000)
							{
								while((PIND & 0x04) == 0);
								PORTD = ~(1<<PD5);
							}
						}
						else
						{
							powerOffRepeat = 0;
						}
						
				}
			} while (bytesWritten < br);
			
			if (br < sizeBlock)
			{
				_delay_ms(100);
				return 0;
			}
		}
	}
	
	return 0;
}

void PeepNtimes(int times)
{
	for (int i=0; i<=times; i++) {
		StartSineTest();
		_delay_ms(200);
		StopSineTest();
		_delay_ms(200);	
	}
}

int main(void)
{
	_delay_ms(10);

	DDRD = 0x22; // PD5 is the output for the power switch
	PORTD = 0xFF;	// all pins high + enable the pull up resistors for the 3 Keys (PD0..PD2)

	
	DDRC = 0b00101001;
	// PC0 -> XDCS (Out)
	// PC1 -> DREQ (In)
	// PC2 -> 
	// PC3 -> XRESET (Out)
	// PC4 -> SDA (??)
	// PC5 -> SCL (??)
	// PC6 -> 
	// PC7 ->

	PORTC = 0xFF;
	_delay_ms(50);
	
	char cText[128] = {0};

//	loop_until_bit_is_set(PIND, PD0);
	
	InitKeyboard();
//	PORTD |= 0x07;	// enable the pull up resistors for the 3 Keys
	
	InitUART();
	SendString("UART running....");
	//while (1) {
		//SendString("Hallo Welt");
		//_delay_ms(2000);
	//}
	
	BYTE res = 0;
	FATFS fs;			/* File system object */
	FRESULT fResult = -1;
	


	res = disk_initialize(); // this also init's the SPI-Interface


	_delay_ms(10);
	HardwareReset();
	SendString("Hardware reset...");


	InitVS1011e();
	SendString("InitVS1011e...");

	_delay_ms(50);

	//while(1)
	//{
		//StartSineTest();
		//_delay_ms(5000);
		//StopSineTest();
		//_delay_ms(2000);
	//}

	fResult = pf_mount(&fs);

	sprintf(cText, "pf_mount: %d",fResult);

	SendString(cText);
	memset(cText, 0, 128);

	if (fResult == 0)
	{
	PORTD = 0xFF;
		uint8_t numFiles = GetNumberFiles();
		uint8_t file2Play = 1;

		sprintf(cText, "Files: %d",numFiles);

		SendString(cText);
		memset(cText, 0, 128);
	
		// in Main function
		while(1)
		{
			uint8_t ret = PlayFile(file2Play);
			switch(ret)
			{
				case BACK:
					file2Play--;
					if (file2Play < 1)
					file2Play = numFiles;
					sprintf(cText, "Back: %d",file2Play);
					SendString(cText);
					memset(cText, 0, 128);
					break;
				case PLAY:
					SendString("Play 1");

					_delay_ms(500);
					//if ((PIND & 0x10) == 0 ) // switch MP3-Player off
					//{
						//PORTD = ~(1<<PD5);
					//}
					while(GetKey() != PLAY)
					{
					}
					_delay_ms(100);
					SendString("Play 2");
					break;
				case FORWARD:
					file2Play++;
					if (file2Play > numFiles)
						file2Play = 1;
					sprintf(cText, "Forward: %d",file2Play);
					SendString(cText);
					memset(cText, 0, 128);
					break;
				//case VOLUME_MINUS:
					//VolumeMinus();
					//break;
				//case VOLUME_PLUS:
					//VolumePlus();
					//break;
				default:
					file2Play++;
					if (file2Play > numFiles)
					file2Play = 1;
					sprintf(cText, "Default: %d",file2Play);
					SendString(cText);
					memset(cText, 0, 128);
					break;
			}
		}
	}
	else
	{
		pf_mount(0);

		PeepNtimes(3);
		// switch of MP3-Player again.
		PORTD = ~(1<<PD5);
		while(1)
		{
		}
	}
	
	_delay_ms(2000);
	
	while(1)
	{
	}
}

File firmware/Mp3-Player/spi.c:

/*
 * spi.c
 *
 * Created: 12.12.2011 21:47:15
 *  Author: Markus
 */ 
#include "spi.h"
#include <util/delay.h>
#include <avr/io.h>

void init_spi (void)
{

	DDRB = (1<<PB1) | (1<<PB2) | (1<<PB3) |(1<<PB5);	// this is for the MP3-Chip
	// PB0 -> NC
	// PB1 -> CS SD-Card (Out)
	// PB2 -> XCS (Out)
	// PB3 -> MOSI (Out)
	// PB4 -> MISO (In)
	// PB5 -> SCK (Out)

	DDRD |= (1<<PD4);	// CS Card
	
	PORTB = ~((1<<PB4));
	
	SPCR = (1<<SPE)|(1<<MSTR)|(1<<SPR0); //Enable SPI, SPI in Master Mode
	
	SPSR = 0x01; // fosz/2
}

void xmit_spi (BYTE byte)
{
	SPDR = byte;
	
	while(!(SPSR & (1<<SPIF)))
	{
	}	
}

BYTE rcv_spi (void)
{
	char Byte = 0;
	SPDR = 0xff;
	
	while(!(SPSR & (1<<SPIF)))
	{
	}
	
	Byte = SPDR;
	
	return Byte;
}

void dly_100us(void)
{
	_delay_us(1);
}

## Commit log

2019-05-24 first working version after redesign
2019-05-24 test
2019-05-24 Layout Hinzugefügt
2019-09-27 updated version from Herbert
2019-10-05 added EvaluationBoard Labor
2019-10-09 update schematic
2019-10-11 DisplayTest added
2019-10-12 update pcb
2019-10-12 pcb finished, 1st version
2019-10-12 pcb finished and order sent to jlcpcb
2019-10-22 GPIO und Serial Test programs added
2020-01-17 rework of keyboard handling
    added function to switch off the MP3-Player
2020-10-26 Sinus removed in case of error
2021-01-22 Bauteilliste mit Fotos (von Schüler)
2021-01-29 Anleitung Gehäuse hinzugefügt
2021-02-05 Bauanleitung hinzugefügt
2021-06-18 Gravur Files added
2023-04-14 Sinus in case that SD-card cannot be read added
    3 peep when SD card mount fails and then shutdown the player
2023-09-28 PDF of schematic added

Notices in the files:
parts and their libraries:
LinearTechnology: Copyright (c) 2013, Michael Hohl
diy-modules: Released under the Creative Commons Attribution 4.0 International License: http://creativecommons.org/licenses/by/4.0
